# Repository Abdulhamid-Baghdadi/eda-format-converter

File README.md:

# EDA Format Converter

*KiCad ⇄ Eagle ⇄ EasyEDA, and from Altium, in the browser*

A converter for **schematics, PCB boards, symbols and footprints** between **KiCad**, **Eagle / Fusion Electronics** and **EasyEDA Standard** in any direction, and from **Altium Designer** into any of them. Drop a file in the [web app](https://abdulhamid-baghdadi.github.io/eda-format-converter/), choose a target format, and compare the source and the converted result side by side before you download it. Everything runs in your browser, so your designs are never uploaded. The same code also runs as a command-line tool.

**▶ Open it: [abdulhamid-baghdadi.github.io/eda-format-converter](https://abdulhamid-baghdadi.github.io/eda-format-converter/)**, then drop your files or try one of the samples.

**Features**
- **Any source, any target.** Each format has a reader *and* a writer built on one shared model, so KiCad, Eagle and EasyEDA can each be the source or the target (9 directions, including same-format conversions that clean up or upgrade a file).
- **Schematics**: placed symbols (rotated, mirrored, multi-unit), wires, junctions, net labels (local, global, hierarchical), power symbols, no-connects, buses and notes, over one or several sheets. Every conversion keeps the netlist, meaning which pins connect to which.
- **Whole boards**: footprints on both sides at any angle, tracks and arcs, vias (blind/buried where the format allows), nets, copper zones and keepouts, board outline, holes, silkscreen and text, inner layers.
- **Libraries**: symbols (pins with type, shape and visibility, multi-unit parts, body graphics) and footprints (SMD/THT/NPTH pads, slots, custom pads, silk/fab/courtyard/mask/paste), with the symbol-to-footprint pin mapping and 3D-model references.
- **Side-by-side preview** of the source and the result, where the result is drawn from the file that was actually written, read back in. Includes layer toggles, synchronised pan and zoom, and a unit selector for multi-unit symbols.
- **A report for every file** listing what was converted, what was approximated and what was skipped, with the reason for each.
- Drag-and-drop single files, several files, or a **.zip** (for example a `.pretty` folder together with its `.kicad_sym`). Download single files or everything as one zip.
- Works **offline** once loaded, has light and dark themes, and works on phones.

## Formats

| Format | Read | Write | Files |
| --- | :-: | :-: | --- |
| **KiCad 6 – 10** | ✅ | ✅ | `.kicad_sch` (a zip for multi-sheet designs), `.kicad_pcb`, `.kicad_mod` (or a zipped `.pretty`), `.kicad_sym` |
| **Eagle 6 – 9 / Fusion Electronics** | ✅ | ✅ | `.sch`, `.brd`, `.lbr` (XML) |
| **EasyEDA Standard** | ✅ | ✅ | schematic, PCB, footprint and symbol `.json` (*File › EasyEDA Source*), and the JSON of a part from EasyEDA's component API |
| **Altium Designer / CircuitMaker** | ✅ | — | `.SchDoc`, `.PcbDoc`, `.PcbLib`, `.SchLib` (binary) |

Altium is read only: it converts to KiCad, Eagle or EasyEDA. Writing Altium files isn't planned, because Altium imports KiCad and Eagle designs itself.

KiCad output uses the **KiCad 8 file format**, which KiCad 8, 9 and 10 all open. Eagle output is Eagle 9 XML. EasyEDA output opens with *File › Open › EasyEDA Source* in EasyEDA Standard.

EasyEDA Pro (`.epro`) files are not converted yet, and the app tells you so when you drop one. See [Roadmap](#roadmap).

## What converts

Each row says what the **target** format can hold. ✅ means exact, ⚠️ means approximated (and listed in the report), ❌ means dropped.

| | to KiCad | to Eagle | to EasyEDA Std |
| --- | --- | --- | --- |
| Footprints: SMD / THT / NPTH pads | ✅ | ✅ | ✅ |
| Pad shapes | ✅ all (trapezoid → rect) | ⚠️ THT pads: round, square, octagon, 2:1 long only | ⚠️ no rounded rect (→ rect) |
| Slotted holes | ✅ | ⚠️ round drill | ✅ |
| Silk / fab / courtyard / mask / paste graphics | ✅ | ✅ | ✅ (courtyard → Mechanical) |
| Arcs, circles, polygons | ✅ | ✅ | ✅ |
| 3D model reference | ✅ | ❌ | ⚠️ name only |
| Symbols: pins (type, shape, hidden), body graphics | ✅ | ✅ | ✅ |
| Multi-unit symbols | ✅ units | ✅ gates | ⚠️ one symbol per unit |
| Symbol ↔ footprint pin mapping | ✅ pad numbers | ✅ `connect`s | ✅ pad numbers |
| Boards: footprints on top and bottom, any angle | ✅ | ✅ | ✅ |
| Tracks, track arcs, vias | ✅ | ✅ | ✅ (through vias only) |
| Nets | ✅ | ✅ signals | ✅ |
| Copper zones, keepouts | ✅ (refill after opening) | ✅ polygons / restrict layers | ✅ copper areas / cutouts |
| Board outline, holes, text | ✅ | ✅ | ✅ |
| Copper layers | ✅ up to 32 | ✅ up to 16 | ✅ up to 34 |
| **Schematics:** symbols, wires, junctions, labels, no-connects | ✅ | ✅ (no-connects dropped) | ✅ |
| Power symbols | ✅ | ✅ supply symbols | ✅ net flags (PWR_FLAG dropped) |
| Multi-sheet / hierarchical designs | ✅ (sheets flattened, hierarchical → global labels) | ✅ sheets | ✅ one file per sheet |
| Buses | ✅ drawn; member nets keep their names | ⚠️ drawn only | ✅ drawn |
| Pin numbers on schematic symbols | ✅ | ⚠️ kept on a placeholder package named after the footprint | ✅ |
| Design rules, net classes, dimensions, images | ❌ | ❌ | ❌ |

### From Altium

The Altium reader takes in:

- **Boards (`.PcbDoc`):** components on both sides, pads (round, rectangular, rounded-rectangle, octagonal, slotted holes), tracks and arcs, vias, nets, polygon pours (as zones), copper regions and fills, polygon cutouts and keepouts, board cutouts, the board outline (with arcs), text, and the inner layers in stack order.
- **Footprint libraries (`.PcbLib`):** the same primitives per footprint. Vias inside a footprint, such as thermal vias in an exposed pad, become unnumbered pads.
- **Symbol libraries (`.SchLib`):** multi-part symbols, pins (type, direction, inverted/clock, hidden), body graphics, the designator prefix, parameters and the linked footprint name.

Some things are approximated or dropped, and each case is listed in the report:

- Mechanical layers go to `Dwgs.User`, because what each one means differs between projects.
- TrueType text is drawn with the target's stroke font.
- 3D bodies, design rules, dimensions, alternate (De Morgan) symbol views and pad-hole offsets are dropped.

### Schematics

Schematics convert between KiCad, Eagle and EasyEDA in any direction, and from Altium `.SchDoc`. What matters in a schematic is its connectivity, so every conversion is checked by comparing netlists (which pins connect to which) before and after. The same connectivity rules are used for every format: wire ends and T-joints, pins touching wires, local labels within a sheet, global and hierarchical labels and power symbols across sheets, and hidden power pins joining the net of their name, as KiCad and Eagle do.

- Hierarchical KiCad designs: drop all the `.kicad_sch` files together, or a zip of the project folder. Sheets are flattened, so hierarchical labels and sheet pins connect by name like global labels.
- Eagle stores pin numbers only on packages. A schematic written to Eagle therefore gets placeholder packages named after each part's footprint (one pad per pin number), and you can swap in the real packages in Eagle.
- Altium and EasyEDA store each placed symbol with its geometry already on the sheet, so each placement becomes its own symbol definition.

## Using it

**In the browser.** Open the [web app](https://abdulhamid-baghdadi.github.io/eda-format-converter/), drop your files, and pick *KiCad*, *Eagle* or *EasyEDA*. The source format is detected from the file contents, so the file extension doesn't matter. Check the preview and the report, then download.

- **KiCad:** a `.kicad_pcb` opens directly; press **B** to refill the zones. Libraries come as a `.kicad_sym` plus a `.pretty` folder. Add both in *Preferences › Manage Symbol/Footprint Libraries*. The symbols' *Footprint* fields already point to `<library>:<footprint>`.
- **Eagle / Fusion:** open the `.brd` or `.lbr`. Libraries contain one device set per symbol, with its package and pin-pad connections.
- **EasyEDA Standard:** *File › Open › EasyEDA Source* and pick the `.json`.

**On the command line** (Node 20+):

```bash
git clone https://github.com/Abdulhamid-Baghdadi/eda-format-converter && cd eda-format-converter
npm install && npm run cli
node dist/cli.mjs board.brd --to kicad --out converted --report
node dist/cli.mjs my-parts.lbr part.json footprints.zip --to easyeda --out converted
```

`--report` prints the same converted / approximated / skipped report the web app shows.

## How it works

```
 .kicad_*  ─┐                                ┌─► .kicad_*
 .brd/.lbr ─┼─► reader ─► neutral model ─► writer ─┼─► .brd/.lbr
 .json     ─┘     (per format)      (per format)   └─► .json
```

- **One model in the middle** ([`src/core/model.ts`](src/core/model.ts)): boards, footprints and symbols in millimetres. Footprints and boards use Y pointing down and symbols use Y pointing up. Layers use KiCad's names (`F.Cu`, `B.SilkS`, `In2.Cu`, `Edge.Cuts`…), the finest common vocabulary of the three formats. Arcs are stored as three points (start, mid, end), so they survive mirroring and rotation without sign mistakes.
- **A reader and a writer per format**, with no direct format-to-format code. Adding a format means writing one reader and one writer, and it then converts to and from all the others.
- **KiCad**: a small S-expression parser and writer ([`kicad/`](src/core/kicad)). It reads KiCad 6 to 10, including KiCad 5 `module`s with centre-angle arcs and KiCad 10 boards that store nets by name. It writes the KiCad 8 format.
- **Eagle**: XML through `fast-xml-parser` ([`eagle/`](src/core/eagle)). This covers wire `curve` arcs, the `MRθ` element transform (rotate, then mirror about Y, as KiCad's own importer does), auto pad and via diameters from the board's design rules, smashed name/value labels, and devices → symbols with gates and connects.
- **EasyEDA Standard**: the `~`-separated shape strings in 10-mil units ([`easyeda/`](src/core/easyeda)), including SVG path arcs, polygon pads, slots, `LIB` footprint instances on boards, and pin paths that give each pin's direction.
- **Altium** ([`altium/`](src/core/altium)): Altium's binary files are OLE compound files. A small reader written from Microsoft's published [MS-CFB] specification opens the container. Inside it, text records (`|KEY=VALUE|`) hold components, nets and the board outline, and little-endian binary records hold pads, tracks, arcs, vias, text, fills and regions, in units of 1/10000 mil. The record layouts were checked against real files and against the Apache-2.0 [AltiumSharp](https://github.com/issus/AltiumSharp) project's documentation of the format. No code from GPL importers was used.
- The **web app** ([`src/web/`](src/web)) is TypeScript and Vite with no UI framework. The previews are SVG drawn from the model. The *result* pane re-reads the written file, so what you see is what was written.

Schematics are checked against KiCad's own netlist: on KiCad's demo schematics, the netlist this project computes matches `kicad-cli sch export netlist`, before and after converting to every format.

The format readers and writers were written for this project from the published file formats and from inspecting real files. No code from GPL or AGPL projects (KiCad's importers, easyeda2kicad) was used, so the project can be MIT licensed.

## How it is tested

`npm test` runs 91 tests ([`tests/`](tests)):

- **Every sample through every format and back** (boards and libraries, 3 × 3), compared geometrically: each pad's world position, size and net, every track and via, and each pin's number, position and direction.
- **In the real KiCad** (when `kicad-cli` is installed): the demo board converted *from KiCad, Eagle and EasyEDA* must pass **KiCad's DRC with zero violations and zero unconnected items** after refilling zones. Converted symbol and footprint libraries must load and plot. **KiCad's own Eagle importer** must place every pad exactly where this project's Eagle reader does.
- **Schematics**: every sample schematic (KiCad, Eagle, EasyEDA, Altium) converts to all three formats without changing a single connection. The 555 schematic has exactly the nets of the 555 board. The Altium schematic matches its Altium board. With KiCad installed, **KiCad's netlist of each converted `.kicad_sch` equals ours**, and the KiCad and Eagle versions pass **KiCad's ERC with no errors**.
- **Altium**: the sample board, footprint and symbol library are read and converted to all three formats without moving any copper or pin, and (with KiCad installed) **KiCad's own Altium importer places every pad, track and via exactly where this reader does**.
- Geometry unit tests: arc conventions of each format, the Eagle rotate/mirror order, and S-expression edge cases.

Wider checks, run locally against files that can't be redistributed:

| Check | Result |
| --- | --- |
| 3,584 symbols and footprints from KiCad's own libraries (QFP, QFN, BGA, TO, USB, headers, MCUs, op-amps, 74xx…) → each format → back | KiCad → KiCad 3583/3584 exact, KiCad → EasyEDA 3584/3584 exact. Eagle: all pads in place; 1,749 footprints have oval or rectangular through-hole pads that Eagle can't represent exactly (reported). |
| KiCad demo boards (`video` 2,118 pads / 7,932 tracks / 808 vias, `StickHub` with parts at 45° on the bottom, `kit-dev-coldfire`) → Eagle → KiCad's Eagle importer | 0 pad, track or via differences from this project's Eagle reader |
| The same boards → EasyEDA → back, and → KiCad → back | 0 differences |
| A real Eagle 7.7 board (a controller board from a student project) → KiCad, compared with KiCad's own import of the same `.brd` | 119/119 pads identical in position, size and net |
| 182 symbols and packages from real Eagle libraries → all three formats → back | 182/182 exact |
| KiCad's demo schematics `ecc83`, `interf_u` (110 nets) and `sonde xilinx` → this reader, and → KiCad, Eagle and EasyEDA → back | Identical to KiCad's own netlist, before and after every conversion |
| Hierarchical KiCad demos with buses (`pic_programmer`, `kit-dev-coldfire`) | `pic_programmer`: 33 of 34 nets identical (one pin differs). Bus-heavy hierarchies are approximate, see Limitations. |
| 8 Altium schematics (AltiumSharp test data) compared with the nets of their own Altium boards | 75/75 schematic nets sit on exactly one board net |
| 4 real Altium boards (MAX5719 breakout, VCOCXO breakout, SPI isolator, USB power adapter; 2 and 4 layers): this reader compared with KiCad's own Altium importer | 517/517 pads identical (position, size, net), 1,162 tracks and 1,898 vias identical. Two panel files, which only place copies of other boards, are reported as not converted. |
| 11 Altium footprints (BGA-900, BGA-676, UFBGA, WLCSP, LFCSP, QFN…) compared with AltiumSharp's JSON dumps of the same files | 2,118/2,118 pads identical in name, position and size |
| 21 Altium footprints and symbols (incl. the 21-unit Raspberry Pi CM4 symbol) → KiCad and EasyEDA → back | 21/21 exact; the KiCad symbols load and plot in KiCad 10 |
| 4 parts from EasyEDA's library (STM32F103, RP2040, a USB-C socket, a 0603 resistor: 8 symbols and footprints) → each format → back, and opened in KiCad 10 | 8/8 exact through KiCad and EasyEDA; all load and plot in KiCad |

## Samples

The app's first samples are **whole projects**: a zip with the schematic and the board, in KiCad, Eagle, EasyEDA and Altium form. Both convert together and show as *Schematic* and *Board layout* tabs. You can drop your own project zip, or several files at once, the same way.

[`public/samples/`](public/samples) has small, freely licensed files to try. The app has a button for each one:

- **`blinky-555`** is a 555 LED blinker: a **schematic** (`.kicad_sch`, Eagle `.sch`, EasyEDA `.schematic.json`) and its 2-layer board (39 × 20 mm, SOIC-8, 0805 parts, a pin header, one part on the bottom at 45°, a GND pour on the bottom layer, and rounded corners), in KiCad, Eagle and EasyEDA versions. It was built for this project from footprints in the official KiCad library ([`scripts/make-samples.ts`](scripts/make-samples.ts)).
- **`demo-parts.lbr`** is a hand-written Eagle library: a resistor, a dual op-amp with three gates, an LDO, an NPN transistor, a header, and a GND supply symbol.
- **`SOT-23-5_regulator.json`** is a hand-made EasyEDA Standard part (symbol and footprint), laid out like EasyEDA's own JSON.
- **Altium:** **`usb-power-adapter.SchDoc`** and **`usb-power-adapter.PcbDoc`** (a schematic and its 2-layer board) and **`QFN-24_4x4.PcbLib`** (a QFN-24 footprint) come from the [AltiumSharp](https://github.com/issus/AltiumSharp) test data (Apache-2.0). **`CM4.SchLib`** (the 21-unit Raspberry Pi CM4 symbol) comes from QWaveSystems' [CM4 Altium library](https://github.com/QWaveSystems/QWAVE_Raspberry-Pi-CM4-Altium-Library) (MIT). See [`public/samples/THIRD_PARTY.md`](public/samples/THIRD_PARTY.md).
- **`demo-parts.zip`** is a hand-written KiCad library (`.kicad_sym` + `.pretty`) with a multi-unit op-amp, an LED, a SOIC-8, and a terminal block with a slot.

## Limitations

- **Schematics:** hierarchy is flattened. Bus member nets that cross hierarchical sheets are matched by name, which fits most designs, but large bus-heavy hierarchies can differ from KiCad by a few pins. Eagle has no no-connect marker, and EasyEDA has no PWR_FLAG. Altium sheet symbols are not expanded, so convert each `.SchDoc`.
- **EasyEDA Pro** files are not converted yet.
- **Altium is input only**, and only binary files are read (not the ASCII `.PcbDoc` variant). Altium's newer "shape-based" regions duplicate the normal ones and are ignored. Panels made of embedded boards are not expanded, so open the board itself.
- **Zones are written unfilled.** Refill them in the target tool (KiCad: **B**). Thermal relief settings, net classes and design rules are not carried over.
- **Eagle through-hole pads** can only be round, square, octagonal, or "long" with a fixed 2:1 ratio. Other ovals and rectangles become the nearest Eagle shape, and slots become round drills (all listed in the report).
- **EasyEDA Standard** has no rounded-rectangle pads (they become rectangles) and stores one symbol per unit. 3D models stay on EasyEDA's server, so only the model's name is carried over. You can get the STEP with the [KiCad JLCPCB part picker](https://github.com/Abdulhamid-Baghdadi/kicad-jlcpcb-part-picker).
- **Text** uses each tool's own stroke font, so text widths differ slightly. Where formats anchor text differently, the position is converted with an estimated text width.
- Dimensions, images, groups and variants are dropped.

## Roadmap

- Full bus semantics for hierarchical schematics, and keeping hierarchy (rather than flattening it) when writing KiCad.
- EasyEDA Pro (`.epro` / `.elibz`), PADS ASCII (read and write), and IPC-2581 (the open manufacturing exchange standard).
- Exporting design rules and net classes where formats share them.

## Development

```bash
npm install
npm run dev        # web app on http://localhost:5173
npm test           # unit and round-trip tests (+ kicad-cli checks if KiCad is installed)
npm run build      # static site in site/ (deployed to GitHub Pages by .github/workflows/pages.yml)
npm run samples    # rebuild the demo board from KiCad's footprint library
```

## Licence

[MIT](LICENSE). The demo board uses footprints from the [KiCad library](https://gitlab.com/kicad/libraries/kicad-footprints) (CC-BY-SA 4.0 with an exception that allows designs made with them to be distributed freely). KiCad, Eagle, Fusion and EasyEDA are trademarks of their owners, and this project is not affiliated with any of them.

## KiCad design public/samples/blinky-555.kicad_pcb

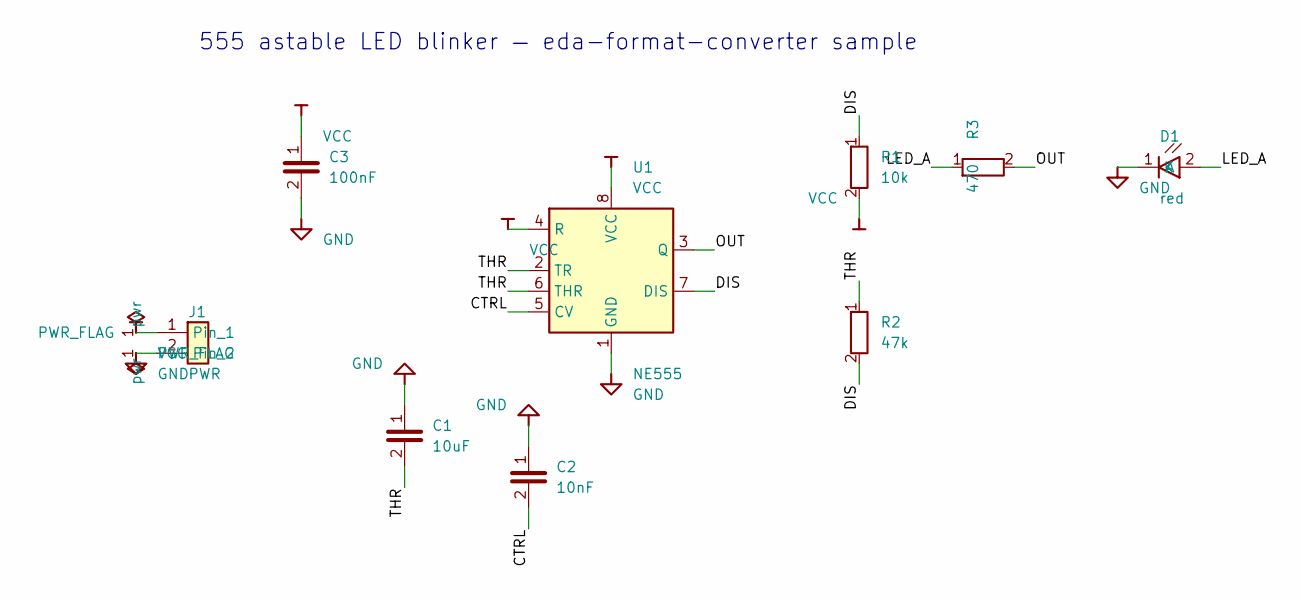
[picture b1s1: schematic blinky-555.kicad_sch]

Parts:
C1: 10uF; C_0805_2012Metric
C2: 10nF; C_0805_2012Metric
C3: 100nF; C_0603_1608Metric
D1: red; LED_0805_2012Metric
J1: PWR; PinHeader_1x02_P2.54mm_Vertical
R1: 10k; R_0805_2012Metric
R2: 47k; R_0805_2012Metric
R3: 470; R_0805_2012Metric
U1: NE555; SOIC-8_3.9x4.9mm_P1.27mm

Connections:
CTRL: C2.2, U1.5 (CV)
DIS: R1.1, R2.2, U1.7 (DIS)
GND: C1.1, C2.1, C3.2, D1.1 (K), J1.2, U1.1 (GND)
LED_A: D1.2 (A), R3.1
OUT: R3.2, U1.3 (Q)
THR: C1.2, R2.1, U1.2 (TR), U1.6 (THR)
VCC: C3.1, J1.1, R1.2, U1.4 (R), U1.8 (VCC)

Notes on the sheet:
555 astable LED blinker — eda-format-converter sample

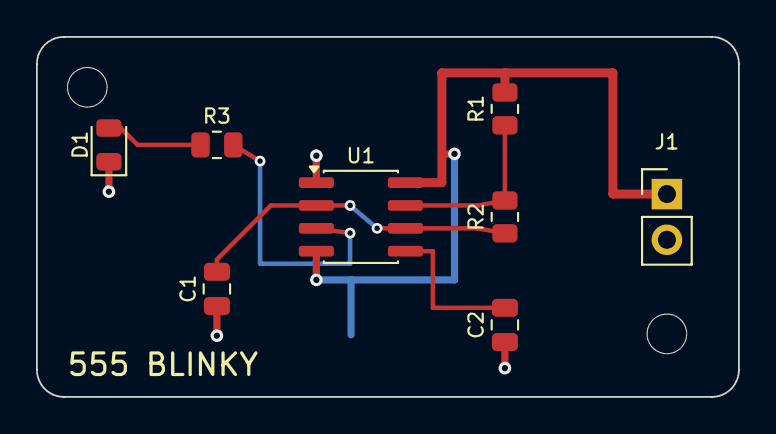
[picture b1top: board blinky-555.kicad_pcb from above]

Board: 2 copper layers, 39.0 x 20.0 mm, 11 parts (1 on the bottom side), 7 nets.

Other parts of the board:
H: Hole; MountingHole
H#2: Hole; MountingHole
